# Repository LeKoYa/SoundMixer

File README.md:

# SoundMixer
A deej-powered Soundmixer for individual volume control with rotary encoders, leds, buttons and oled support. I've also made an enclosure that is supposed to be mounted below a table.

This is still an early version and rebuilding your own might become very tricky. I am actively working on a second version that will be easier to build and assemble.

# Hardware
The soundmixer uses the following things:
- Arduino nano
- 5x Custom PCBs with 25 ws2812 LEDs and rotary encoder
- 1x 1.3" i2c oled screen (ssd1306)
- 2x mx-switch
- 2x pull-up resistors
- A lot of cables

### LED-PCB
For the LEDs i've designed a custom pcb with a size of 3x3cm. On the front side are 25 1010 ws2812 LEDs, neatly arranged around a rotary encoder (PEC11R-4015F-S0024). The backside features some capacitors and resistors used mainly for the encoder. It also features a small 7-pin molex picoblade connector due to the limited space.

The pcb was designed in kicad. I am still working on a version2 that features two pcbs stacked on top of each other, so the encoder does not stick out too far above the leds.

### Enclosure
The entire enclosure is 3d-printed, mainly in PLA. The diffusers in front of the led rings are made out of translucent PETG.
The parts are screwed together with some M2.5 screws. 

# Software

### PC Side
On the pc side, it uses a fork of the original deej project [found here](https://github.com/michaelwschultz/deej). 

### Arduino Side
For the arduino i wrote my own firmware (see the [software](Software) folder), with the help of platformio using some arduino libraries.

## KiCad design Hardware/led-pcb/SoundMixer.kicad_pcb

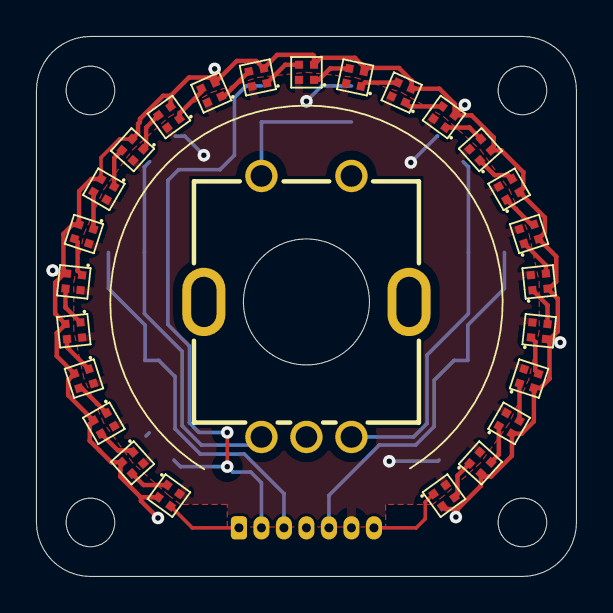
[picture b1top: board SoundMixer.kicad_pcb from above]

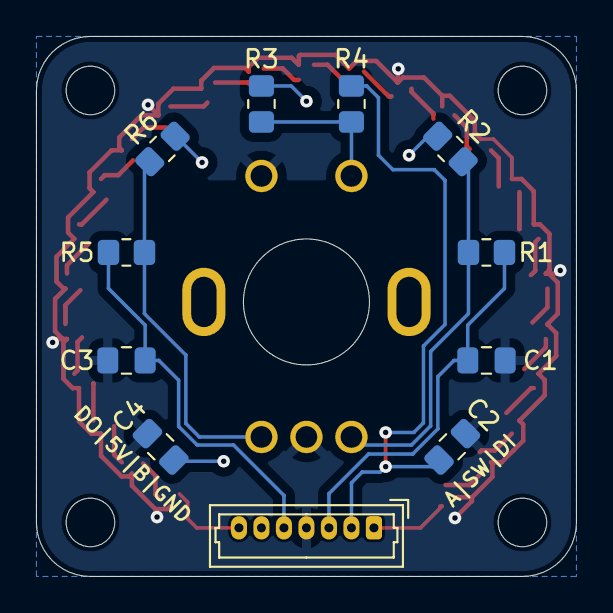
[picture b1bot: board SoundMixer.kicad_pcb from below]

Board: 2 copper layers, 30.0 x 30.0 mm, 41 parts (11 on the bottom side), 34 nets.

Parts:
C1, C2, C3: 0.01uF; C_0805_2012Metric_Pad1.18x1.45mm_HandSolder
C4: 4.7uF; C_0805_2012Metric_Pad1.18x1.45mm_HandSolder
H1, H2, H3, H4: MountingHole; MountingHole_2.7mm_M2.5
J1: Conn_01x07; Molex_PicoBlade_53047-0710_1x07_P1.25mm_Vertical
R1, R2, R3, R5, R6: 10K; R_0805_2012Metric_Pad1.20x1.40mm_HandSolder
R4: 1K; R_0805_2012Metric_Pad1.20x1.40mm_HandSolder
SW1: PEC11R-4015F-S0024; SW-TH_PEC11R-4XXXF-SXXXX
U1, U2, U3, U4, U5, U6, U7, U8, U9, U10, U11, U12, U13, U14, U15, U16, U17, U18, U19, U20, U21, U22, U23, U24, U25: XL-1010RGBC-WS2812B; LED-SMD_4P-L1.0-W1.0-TL_XL-1010RGBC-WS2812B

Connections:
/Encoder_A: C1.1, J1.3, R1.1
/Encoder_B: C3.1, J1.5, R5.2
/Encoder_Button: C2.1, J1.2, R4.2
DIN: J1.1, U1.4 (DIN)
DOUT: J1.7, U25.1 (DOUT)
GND: C1.2, C2.2, C3.2, C4.2, J1.4, SW1.2, SW1.C, U1.3 (GND), U2.3 (GND), U3.3 (GND), U4.3 (GND), U5.3 (GND), U6.3 (GND), U7.3 (GND), U8.3 (GND), U9.3 (GND), U10.3 (GND), U11.3 (GND), U12.3 (GND), U13.3 (GND), U14.3 (GND), U15.3 (GND), U16.3 (GND), U17.3 (GND), U18.3 (GND), U19.3 (GND), U20.3 (GND), U21.3 (GND), U22.3 (GND), U23.3 (GND), U24.3 (GND), U25.3 (GND)
unnamed: R1.2, R2.1, SW1.A
unnamed: R3.2, R4.1, SW1.1
unnamed: R5.1, R6.1, SW1.B
unnamed: U1.1 (DOUT), U2.4 (DIN)
unnamed: U2.1 (DOUT), U3.4 (DIN)
unnamed: U3.1 (DOUT), U4.4 (DIN)
unnamed: U4.1 (DOUT), U5.4 (DIN)
unnamed: U5.1 (DOUT), U6.4 (DIN)
unnamed: U6.1 (DOUT), U7.4 (DIN)
unnamed: U7.1 (DOUT), U8.4 (DIN)
unnamed: U8.1 (DOUT), U9.4 (DIN)
unnamed: U9.1 (DOUT), U10.4 (DIN)
unnamed: U10.1 (DOUT), U11.4 (DIN)
unnamed: U11.1 (DOUT), U12.4 (DIN)
unnamed: U12.1 (DOUT), U13.4 (DIN)
unnamed: U13.1 (DOUT), U14.4 (DIN)
unnamed: U14.1 (DOUT), U15.4 (DIN)
unnamed: U15.1 (DOUT), U16.4 (DIN)
unnamed: U16.1 (DOUT), U17.4 (DIN)
unnamed: U17.1 (DOUT), U18.4 (DIN)
unnamed: U18.1 (DOUT), U19.4 (DIN)
unnamed: U19.1 (DOUT), U20.4 (DIN)
unnamed: U20.1 (DOUT), U21.4 (DIN)
unnamed: U21.1 (DOUT), U22.4 (DIN)
unnamed: U22.1 (DOUT), U23.4 (DIN)
unnamed: U23.1 (DOUT), U24.4 (DIN)
unnamed: U24.1 (DOUT), U25.4 (DIN)
VCC: C4.1, J1.6, R2.2, R3.1, R6.2, U1.2 (VDD), U2.2 (VDD), U3.2 (VDD), U4.2 (VDD), U5.2 (VDD), U6.2 (VDD), U7.2 (VDD), U8.2 (VDD), U9.2 (VDD), U10.2 (VDD), U11.2 (VDD), U12.2 (VDD), U13.2 (VDD), U14.2 (VDD), U15.2 (VDD), U16.2 (VDD), U17.2 (VDD), U18.2 (VDD), U19.2 (VDD), U20.2 (VDD), U21.2 (VDD), U22.2 (VDD), U23.2 (VDD), U24.2 (VDD), U25.2 (VDD)

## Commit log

2025-07-11 Added the kicad files of the led-pcb
